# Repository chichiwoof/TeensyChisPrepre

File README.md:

View this project on [CADLAB.io](https://cadlab.io/project/22775). 

# TeensyChisPrepre

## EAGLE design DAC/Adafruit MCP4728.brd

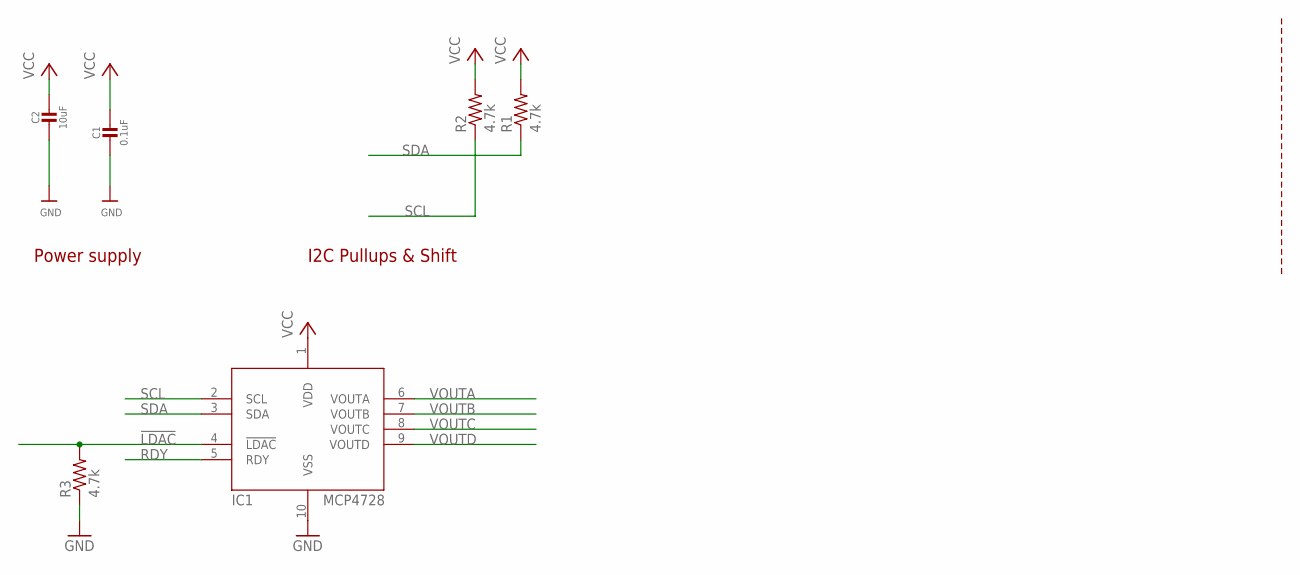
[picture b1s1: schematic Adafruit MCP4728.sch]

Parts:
C1: 0.1uF; 0603-NO
C2: 10uF; 0805-NO
IC1: MCP4728; MSOP10
R1, R2, R3: 4.7k; 0204/7

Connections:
!LDAC: IC1.4 (!LDAC), R3.2
GND: C1.2, C2.2, IC1.10 (VSS), R3.1
RDY: IC1.5 (RDY)
SCL: IC1.2 (SCL), R2.1
SDA: IC1.3 (SDA), R1.1
VCC: C1.1, C2.1, IC1.1 (VDD), R1.2, R2.2
VOUTA: IC1.6 (VOUTA)
VOUTB: IC1.7 (VOUTB)
VOUTC: IC1.8 (VOUTC)
VOUTD: IC1.9 (VOUTD)

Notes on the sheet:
I2C Pullups & Shift
Power supply

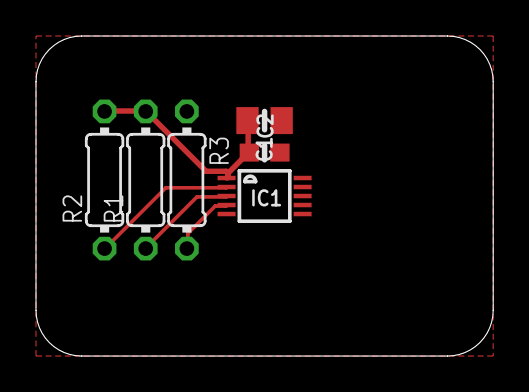
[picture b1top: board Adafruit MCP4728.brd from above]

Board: 2 copper layers, 25.4 x 17.8 mm, 6 parts (0 on the bottom side), 5 nets.

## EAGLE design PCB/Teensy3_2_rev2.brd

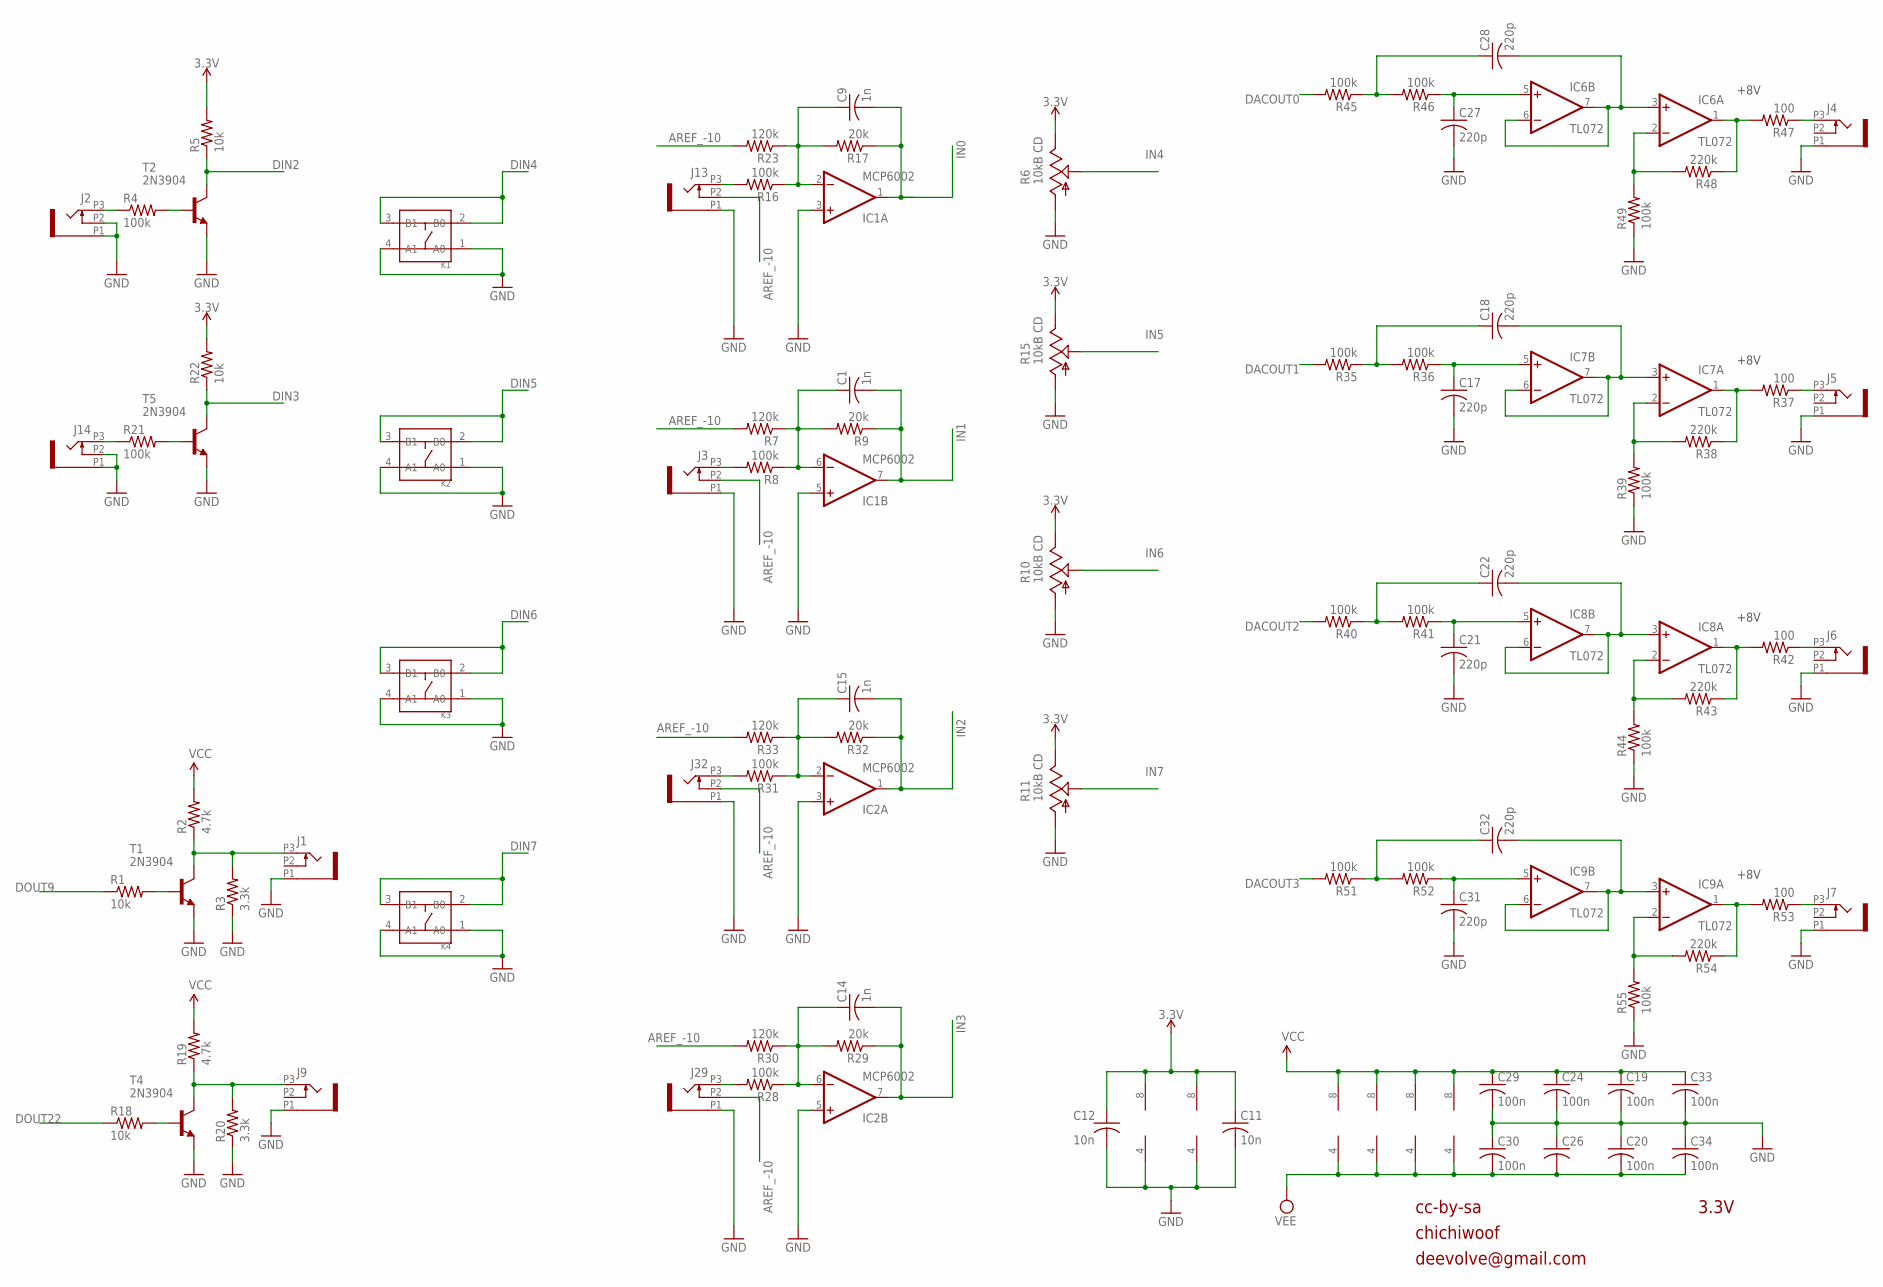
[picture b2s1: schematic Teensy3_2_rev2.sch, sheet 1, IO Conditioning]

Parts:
C1, C9, C14, C15: 1n; C050-025X075
C11, C12: 10n; C050-025X075
C17, C18, C21, C22, C27, C28, C31, C32: 220p; C050-025X075
C19, C20, C24, C26, C29, C30, C33, C34: 100n; C050-025X075
IC1, IC2: MCP6002; SO08
IC6, IC7, IC8, IC9: TL072; SO08
J1, J2, J3, J4, J5, J6, J7, J9, J13, J14, J29, J32: PJ301_THONKICONN6; WQP_PJ_301M6
K1, K2, K3, K4: DIP-SWITCH-TACTILE-SPST-NO/TS-1109(4P-D6.0MM)'TS-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; SW4-6.0X6.0X5.0MM
R1, R5, R18, R22: 10k; 0204/7
R2, R19: 4.7k; 0204/7
R3, R20: 3.3k; 0204/7
R4, R8, R16, R21, R28, R31, R35, R36, R39, R40, R41, R44, R45, R46, R49, R51, R52, R55: 100k; 0204/7
R6, R10, R11, R15: 10kB CD; ALPS_POT_VERTICAL_PS
R7, R23, R30, R33: 120k; 0204/7
R9, R17, R29, R32: 20k; 0204/7
R37, R42, R47, R53: 100; 0204/7
R38, R43, R48, R54: 220k; 0204/7
T1, T2, T4, T5: 2N3904; TO92

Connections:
3.3V: C11.1, C12.1, IC1.8 (V+), IC2.8 (V+), R5.2, R6.P$1 (E), R10.P$1 (E), R11.P$1 (E), R15.P$1 (E), R22.2; also elsewhere on the board
AREF_-10: J3.P2 (2), J13.P2 (2), J29.P2 (2), J32.P2 (2), R7.2, R23.2, R30.2, R33.2; also elsewhere on the board
DACOUT0: R45.2; also elsewhere on the board
DACOUT1: R35.2; also elsewhere on the board
DACOUT2: R40.2; also elsewhere on the board
DACOUT3: R51.2; also elsewhere on the board
DIN2: R5.1, T2.1 (C); also elsewhere on the board
DIN3: R22.1, T5.1 (C); also elsewhere on the board
DIN4: K1.2 (B0), K1.3 (B1); also elsewhere on the board
DIN5: K2.2 (B0), K2.3 (B1); also elsewhere on the board
DIN6: K3.2 (B0), K3.3 (B1); also elsewhere on the board
DIN7: K4.2 (B0), K4.3 (B1); also elsewhere on the board
DOUT9: R1.1; also elsewhere on the board
DOUT22: R18.1; also elsewhere on the board
GND: C11.2, C12.2, C17.2, C19.2, C20.1, C21.2, C24.2, C26.1, C27.2, C29.2, C30.1, C31.2, C33.2, C34.1, IC1.3 (+IN), IC1.4 (V-), IC1.5 (+IN), IC2.3 (+IN), IC2.4 (V-), IC2.5 (+IN), J1.P1 (1), J2.P1 (1), J2.P2 (2), J3.P1 (1), J4.P1 (1), J5.P1 (1), J6.P1 (1), J7.P1 (1), J9.P1 (1), J13.P1 (1), J14.P1 (1), J14.P2 (2), J29.P1 (1), J32.P1 (1), K1.1 (A0), K1.4 (A1), K2.1 (A0), K2.4 (A1), K3.1 (A0), K3.4 (A1), K4.1 (A0), K4.4 (A1), R3.1, R6.P$3 (A), R10.P$3 (A), R11.P$3 (A), R15.P$3 (A), R20.1, R39.1, R44.1, R49.1, R55.1, T1.3 (E), T2.3 (E), T4.3 (E), T5.3 (E); also elsewhere on the board
IN0: C9.2, IC1.1 (OUT), R17.1; also elsewhere on the board
IN1: C1.2, IC1.7 (OUT), R9.1; also elsewhere on the board
IN2: C15.2, IC2.1 (OUT), R32.1; also elsewhere on the board
IN3: C14.2, IC2.7 (OUT), R29.1; also elsewhere on the board
IN4: R6.P$2 (S); also elsewhere on the board
IN5: R15.P$2 (S); also elsewhere on the board
IN6: R10.P$2 (S); also elsewhere on the board
IN7: R11.P$2 (S); also elsewhere on the board
unnamed: R1.2, T1.2 (B)
unnamed: J1.P3 (3), R2.1, R3.2, T1.1 (C)
unnamed: J3.P3 (3), R8.2
unnamed: J13.P3 (3), R16.2
unnamed: C1.1, IC1.6 (-IN), R7.1, R8.1, R9.2
unnamed: C9.1, IC1.2 (-IN), R16.1, R17.2, R23.1
unnamed: R18.2, T4.2 (B)
unnamed: J9.P3 (3), R19.1, R20.2, T4.1 (C)
unnamed: J14.P3 (3), R21.1
unnamed: R21.2, T5.2 (B)
unnamed: J4.P3 (3), R47.1
unnamed: C28.2, IC6.3 (+IN), IC6.6 (-IN), IC6.7 (OUT)
unnamed: C27.1, IC6.5 (+IN), R46.1
unnamed: C28.1, R45.1, R46.2
unnamed: J29.P3 (3), R28.2
unnamed: C14.1, IC2.6 (-IN), R28.1, R29.2, R30.1
unnamed: J32.P3 (3), R31.2
unnamed: C15.1, IC2.2 (-IN), R31.1, R32.2, R33.1
unnamed: C18.2, IC7.3 (+IN), IC7.6 (-IN), IC7.7 (OUT)
unnamed: C17.1, IC7.5 (+IN), R36.1
unnamed: C18.1, R35.1, R36.2
unnamed: IC7.2 (-IN), R38.2, R39.2
unnamed: IC7.1 (OUT), R37.2, R38.1
unnamed: IC6.2 (-IN), R48.2, R49.2
unnamed: IC6.1 (OUT), R47.2, R48.1
unnamed: C22.2, IC8.3 (+IN), IC8.6 (-IN), IC8.7 (OUT)
unnamed: C21.1, IC8.5 (+IN), R41.1
unnamed: C22.1, R40.1, R41.2
unnamed: IC8.2 (-IN), R43.2, R44.2
unnamed: IC8.1 (OUT), R42.2, R43.1
unnamed: C32.2, IC9.3 (+IN), IC9.6 (-IN), IC9.7 (OUT)
unnamed: C31.1, IC9.5 (+IN), R52.1
unnamed: J2.P3 (3), R4.1
unnamed: C32.1, R51.1, R52.2
unnamed: IC9.2 (-IN), R54.2, R55.2
unnamed: IC9.1 (OUT), R53.2, R54.1
unnamed: R4.2, T2.2 (B)
UNI_OUT1: J6.P3 (3), R42.1
UNI_OUT2: J7.P3 (3), R53.1
UNI_OUT3: J5.P3 (3), R37.1
VCC: C19.1, C24.1, C29.1, C33.1, IC6.8 (V+), IC7.8 (V+), IC8.8 (V+), IC9.8 (V+), R2.2, R19.2; also elsewhere on the board
VEE: C20.2, C26.2, C30.2, C34.2, IC6.4 (V-), IC7.4 (V-), IC8.4 (V-), IC9.4 (V-); also elsewhere on the board

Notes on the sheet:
cc-by-sa
3.3V
chichiwoof
deevolve@gmail.com
+8V

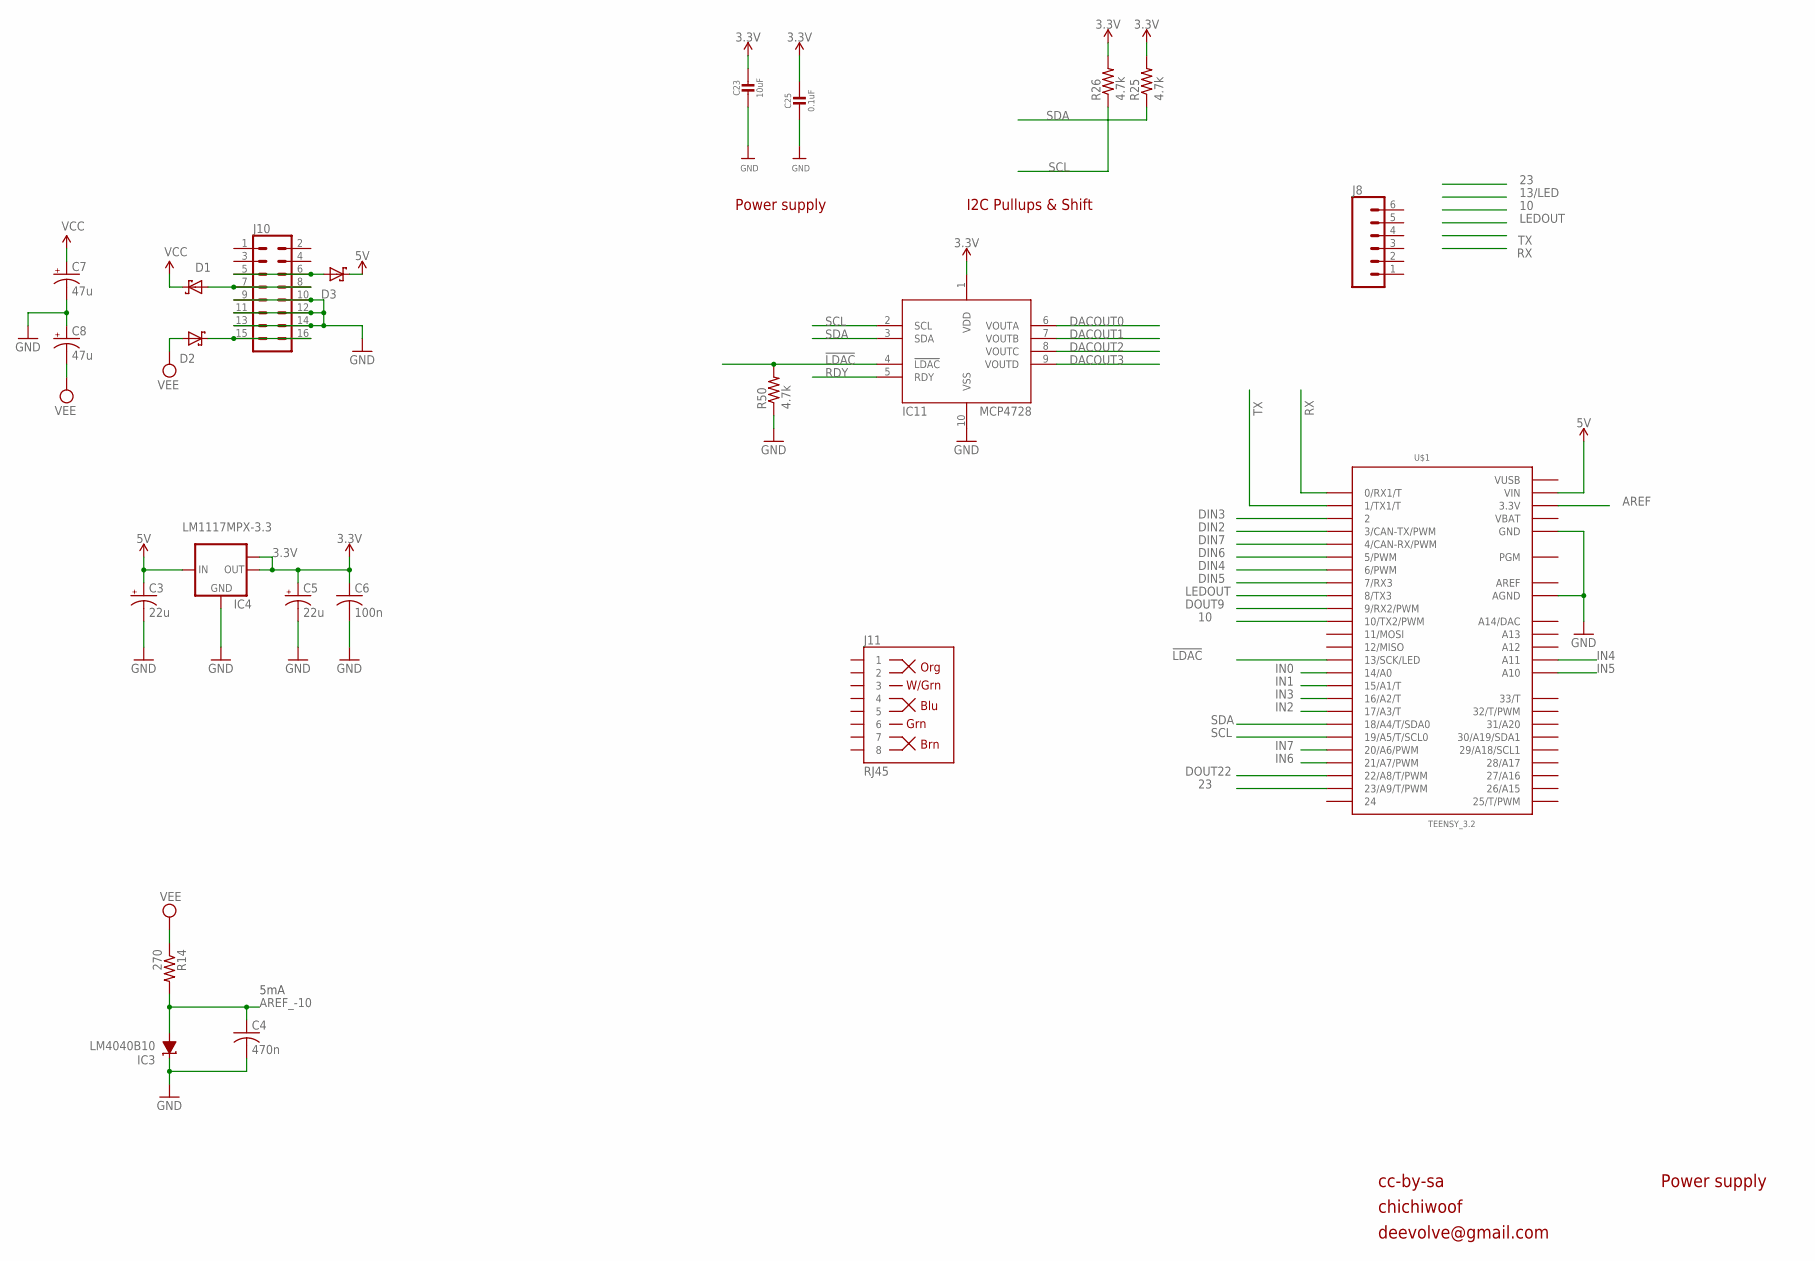
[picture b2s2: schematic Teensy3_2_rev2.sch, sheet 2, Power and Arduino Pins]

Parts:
C3, C5: 22u; E2,5-7
C4: 470n; C050-025X075
C6: 100n; C050-025X075
C7, C8: 47u; E2,5-7
C23: 10uF; 0805-NO
C25: 0.1uF; 0603-NO
D1, D2, D3: 1N5819; DO41-10
IC3: LM4040B10; DBZ_R-PDSO-G3
IC4: LM1117MPX-3.3; SOT223
IC11: MCP4728; MSOP10
J8: CONN_06SILK_FEMALE_PTH; 1X06
J10: CONN_08X2; 2X8
J11: RJ45; RJ45-8
R14: 270; 0204/7
R25, R26, R50: 4.7k; 0204/7
U$1: TEENSY_3.2; TEENSY_3.0-3.2_ALL_PINS_&_PADS

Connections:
3.3V: C5.+, C6.1, C23.1, C25.1, IC4.2 (OUT), IC4.TAB (OUT1), IC11.1 (VDD), R25.2, R26.2; also elsewhere on the board
5V: C3.+, D3.C, IC4.3 (IN), U$1.VIN
10: U$1.10 (10/TX2/PWM)
23: U$1.23/A9 (23/A9/T/PWM)
!LDAC: IC11.4 (!LDAC), R50.2, U$1.13 (13/SCK/LED)
+12: D1.A, J10.7, J10.8
-12: D2.C, J10.15, J10.16
AREF: U$1.3.3V, U$1.3.3V1 (3.3V), U$1.3.3V2 (3.3V), U$1.AREF
AREF_-10: C4.1, IC3.2 (A), R14.2; also elsewhere on the board
DACOUT0: IC11.6 (VOUTA); also elsewhere on the board
DACOUT1: IC11.7 (VOUTB); also elsewhere on the board
DACOUT2: IC11.8 (VOUTC); also elsewhere on the board
DACOUT3: IC11.9 (VOUTD); also elsewhere on the board
DIN2: U$1.3 (3/CAN-TX/PWM); also elsewhere on the board
DIN3: U$1.2; also elsewhere on the board
DIN4: U$1.6 (6/PWM); also elsewhere on the board
DIN5: U$1.7 (7/RX3); also elsewhere on the board
DIN6: U$1.5 (5/PWM); also elsewhere on the board
DIN7: U$1.4 (4/CAN-RX/PWM); also elsewhere on the board
DOUT9: U$1.9 (9/RX2/PWM); also elsewhere on the board
DOUT22: U$1.22/A8 (22/A8/T/PWM); also elsewhere on the board
GND: C3.-, C4.2, C5.-, C6.2, C7.-, C8.+, C23.2, C25.2, IC3.1 (C), IC4.1 (GND), IC11.10 (VSS), J10.9, J10.10, J10.11, J10.12, J10.13, J10.14, R50.1, U$1.AGND, U$1.GND, U$1.GND1 (GND), U$1.GND2 (GND); also elsewhere on the board
IN0: U$1.14/A0; also elsewhere on the board
IN1: U$1.15/A1 (15/A1/T); also elsewhere on the board
IN2: U$1.17/A3 (17/A3/T); also elsewhere on the board
IN3: U$1.16/A2 (16/A2/T); also elsewhere on the board
IN4: U$1.A11; also elsewhere on the board
IN5: U$1.A10; also elsewhere on the board
IN6: U$1.21/A7 (21/A7/PWM); also elsewhere on the board
IN7: U$1.20/A6 (20/A6/PWM); also elsewhere on the board
LEDOUT: U$1.8 (8/TX3)
unnamed: D3.A, J10.5, J10.6
RDY: IC11.5 (RDY)
RX: U$1.0 (0/RX1/T)
SCL: IC11.2 (SCL), R26.1, U$1.19/A5 (19/A5/T/SCL0)
SDA: IC11.3 (SDA), R25.1, U$1.18/A4 (18/A4/T/SDA0)
TX: U$1.1 (1/TX1/T)
VBAT: U$1.VBAT
VCC: C7.+, D1.C; also elsewhere on the board
VEE: C8.-, D2.A, R14.1; also elsewhere on the board
VUSB: U$1.VUSB

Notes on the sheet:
cc-by-sa
Power supply
5mA
chichiwoof
deevolve@gmail.com
I2C Pullups & Shift

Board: 2 copper layers, 116 parts (6 on the bottom side), 73 nets, no tracks yet.

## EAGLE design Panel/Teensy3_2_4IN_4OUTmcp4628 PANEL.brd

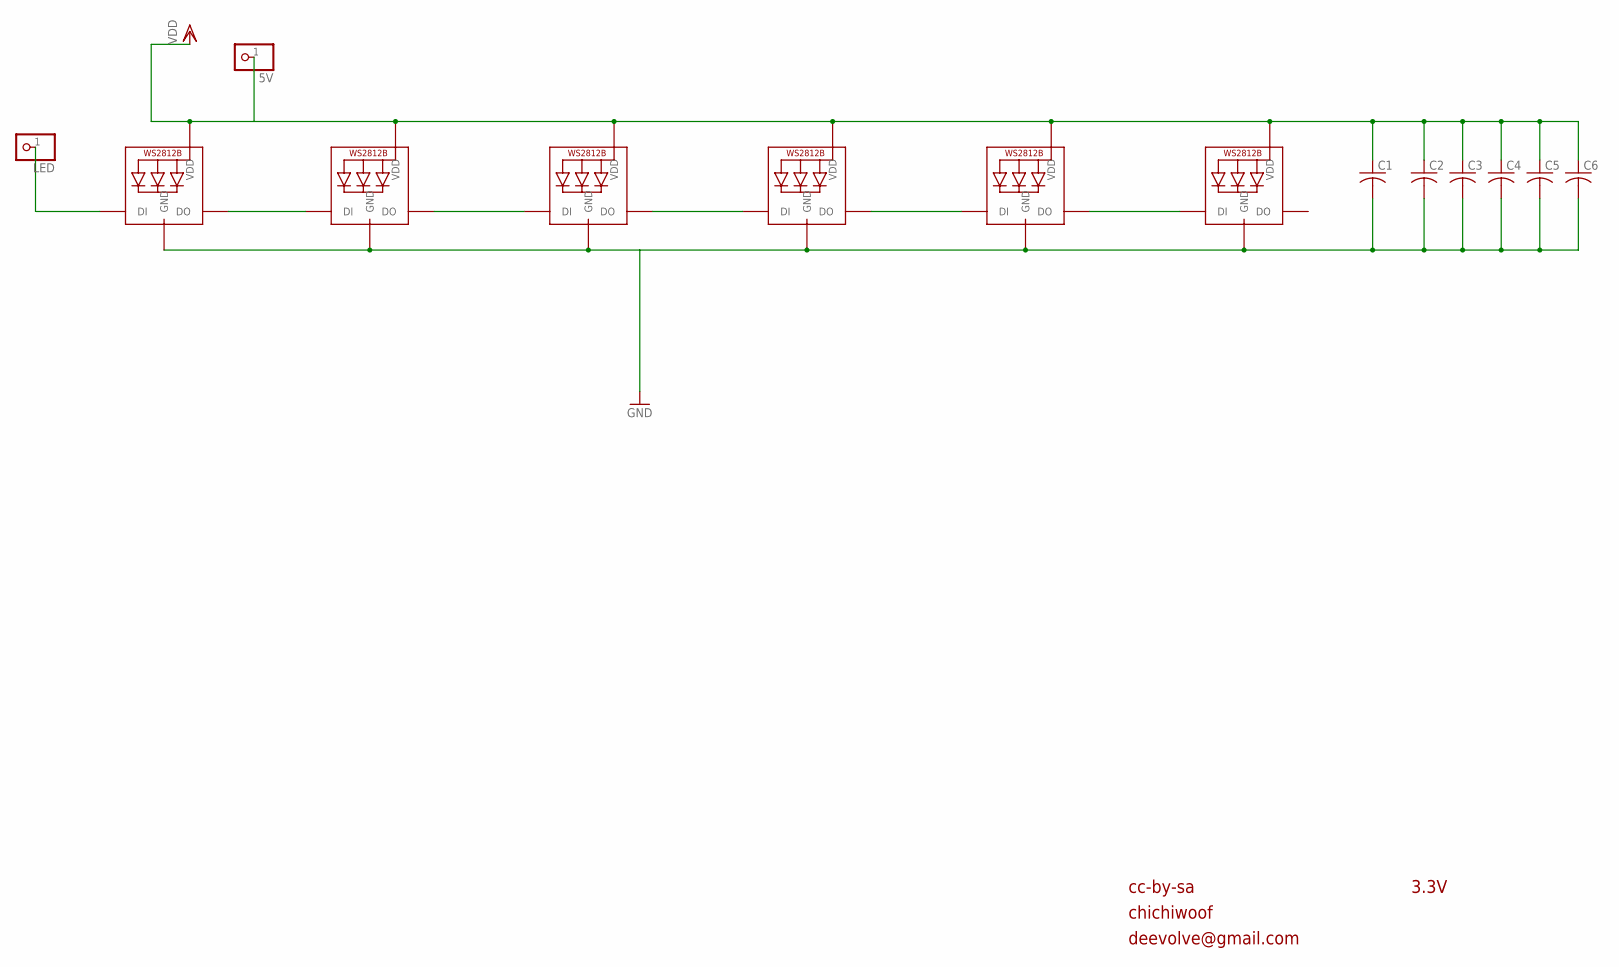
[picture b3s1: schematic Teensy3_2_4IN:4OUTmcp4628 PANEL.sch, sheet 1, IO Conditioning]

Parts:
5V: NEOPIXELRING_PINHD-1X1CB; NEOPIXELRING_1X01-CLEANBIG
C1, C2, C3, C4, C5, C6: C-USC0603; C0603
LED: NEOPIXELRING_PINHD-1X1CB; NEOPIXELRING_1X01-CLEANBIG
LED1, LED2, LED3, LED4, LED5, LED7: WS2812B5050; WS2812B

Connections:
GND: C1.2, C2.2, C3.2, C4.2, C5.2, C6.2, LED1.3-GND (GND), LED2.3-GND (GND), LED3.3-GND (GND), LED4.3-GND (GND), LED5.3-GND (GND), LED7.3-GND (GND)
unnamed: LED1.4-DIN (DI), LED7.2-DOUT (DO)
unnamed: LED1.2-DOUT (DO), LED2.4-DIN (DI)
unnamed: LED2.2-DOUT (DO), LED3.4-DIN (DI)
unnamed: LED3.2-DOUT (DO), LED4.4-DIN (DI)
unnamed: LED4.2-DOUT (DO), LED5.4-DIN (DI)
unnamed: LED.1, LED7.4-DIN (DI)
VDD: 5V.1, C1.1, C2.1, C3.1, C4.1, C5.1, C6.1, LED1.1-VDD (VDD), LED2.1-VDD (VDD), LED3.1-VDD (VDD), LED4.1-VDD (VDD), LED5.1-VDD (VDD), LED7.1-VDD (VDD)

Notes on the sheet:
cc-by-sa
3.3V
chichiwoof
deevolve@gmail.com

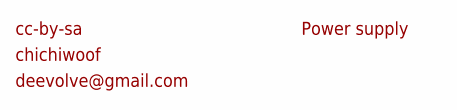
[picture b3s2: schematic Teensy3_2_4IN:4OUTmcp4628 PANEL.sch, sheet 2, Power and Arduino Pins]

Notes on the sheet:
cc-by-sa
Power supply
chichiwoof
deevolve@gmail.com

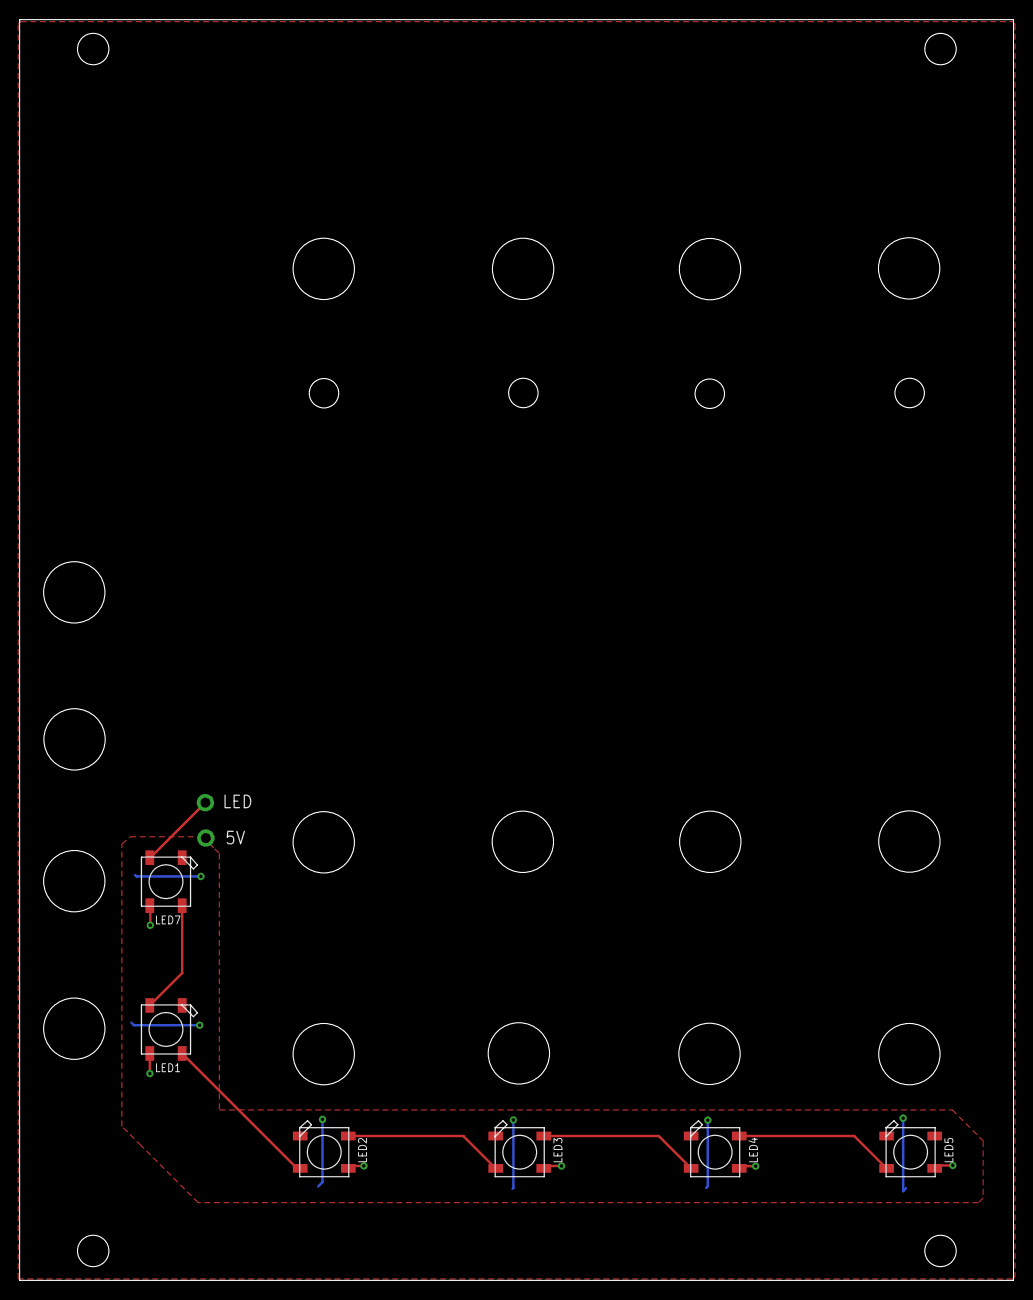
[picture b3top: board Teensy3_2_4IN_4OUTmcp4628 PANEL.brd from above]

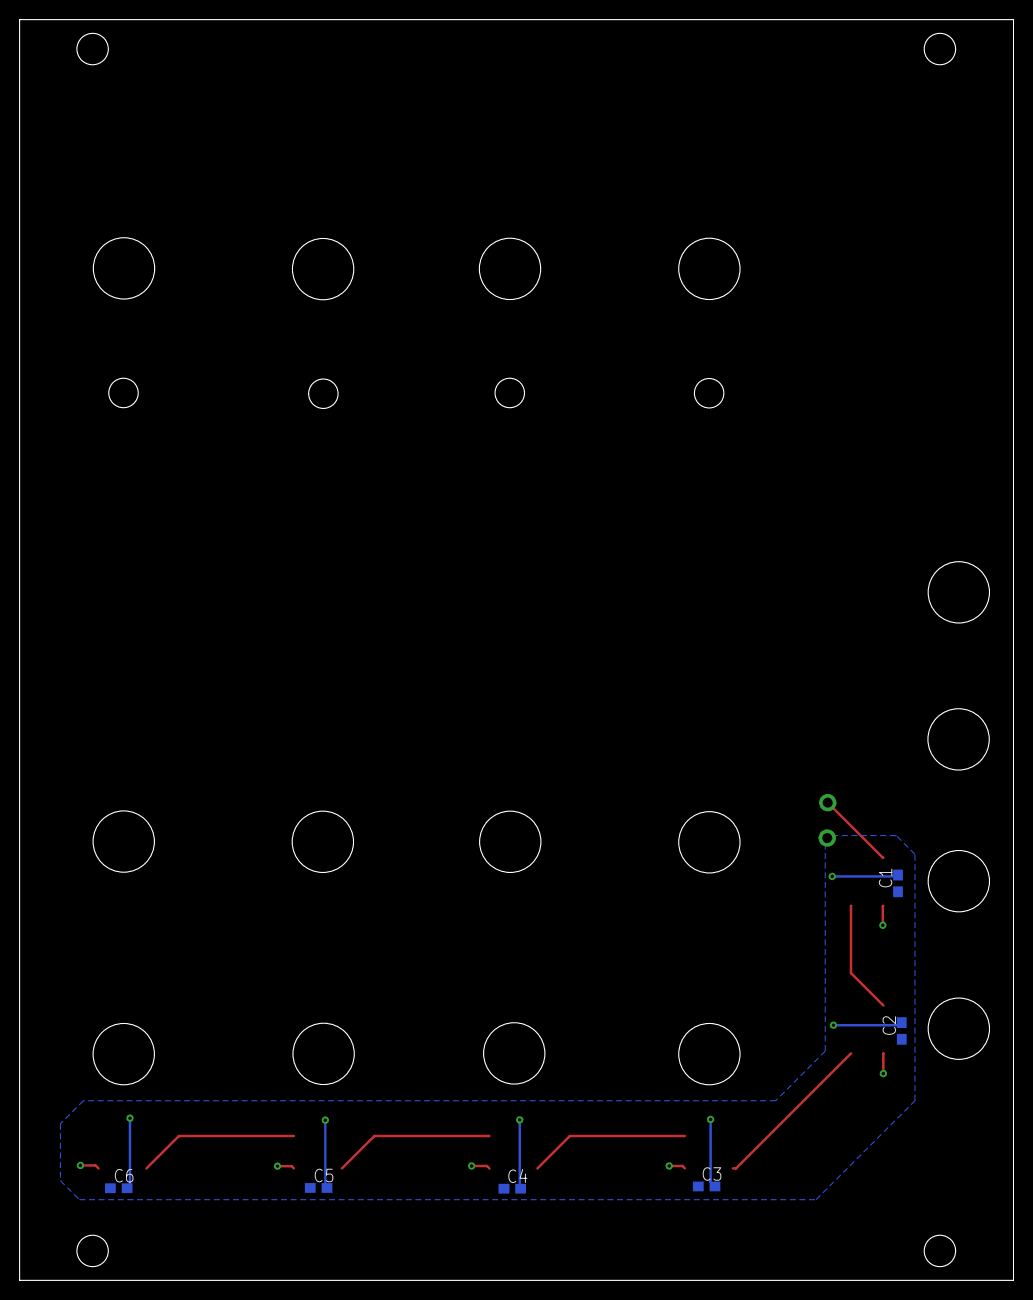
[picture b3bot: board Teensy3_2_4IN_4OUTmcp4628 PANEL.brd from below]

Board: 2 copper layers, 101.3 x 128.5 mm, 14 parts (6 on the bottom side), 8 nets.

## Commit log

2020-04-12 First comm
2020-04-12 Backlink to CADLAB.io has been added.
2020-04-12 organize
2020-04-17 add rev 2
2020-04-30 changed filenames and add superaudioboard
2020-04-30 panel names
2020-05-01 added changes for audio board prepre
2020-05-25 add dac ada

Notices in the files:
parts and their libraries:
microbuilder: This work is placed in the public domain, and may be freely used for commercial and non-commercial work with the following conditions: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
SparkFun-Connectors: Licensing: Creative Commons ShareAlike 4.0 International - https://creativecommons.org/licenses/by-sa/4.0
